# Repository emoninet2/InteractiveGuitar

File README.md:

# InteractiveGuitar

Check documentation on https://github.com/emoninet2/InteractiveGuitar/wiki

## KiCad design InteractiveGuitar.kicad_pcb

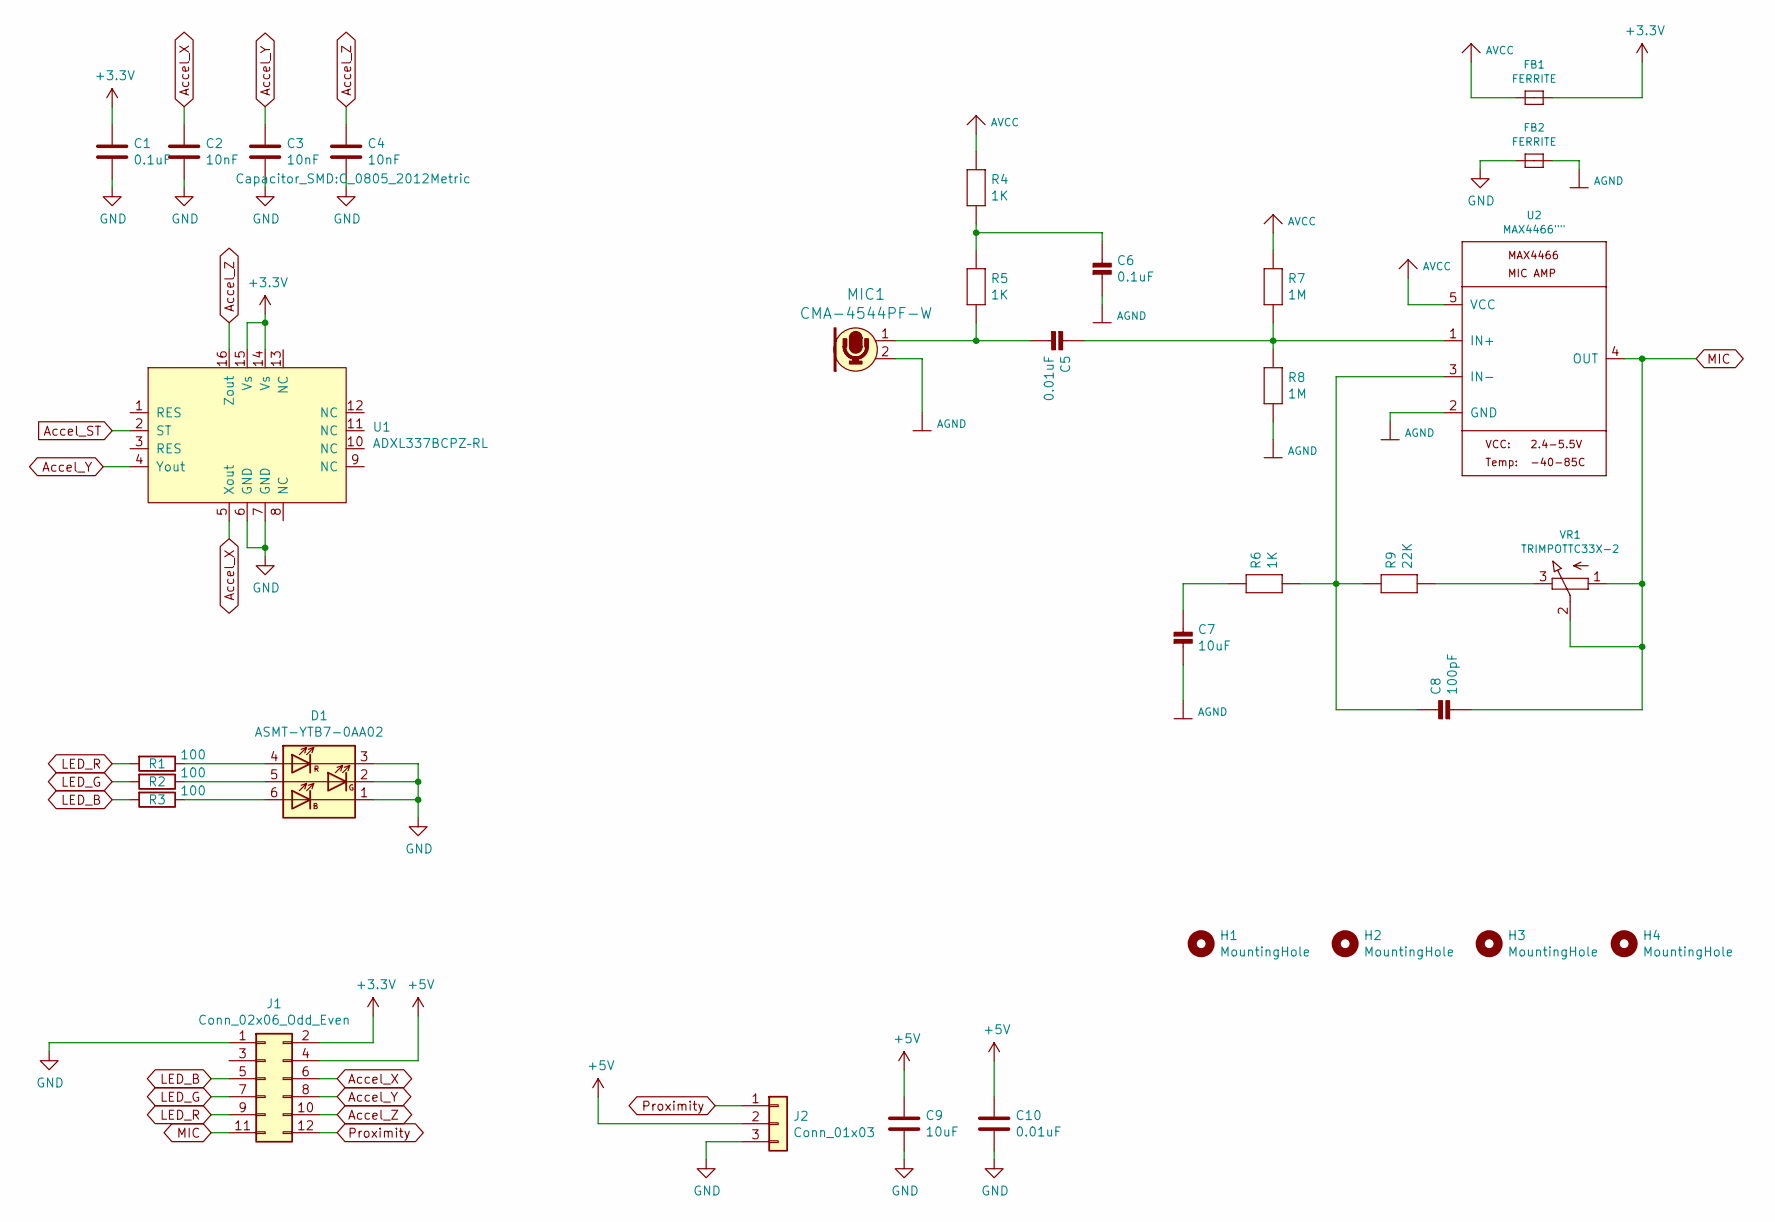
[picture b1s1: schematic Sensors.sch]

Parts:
C1: 0.1uF; C_0805_2012Metric
C2, C3, C4: 10nF; C_0805_2012Metric
C5: 0.01uF; 0805
C6: 0.1uF; 0805
C7: 10uF; 0805
C8: 100pF; 0805
C9: 10uF; C_0805_2012Metric
C10: 0.01uF; C_0805_2012Metric
D1: ASMT-YTB7-0AA02; LED_RGB_5050-6
FB1, FB2: FERRITE; 0805
H1, H2, H3, H4: MountingHole; MountingHole_2.2mm_M2_DIN965_Pad
J1: Conn_02x06_Odd_Even; PinHeader_2x06_P2.54mm_Horizontal
J2: Conn_01x03; PinHeader_1x03_P2.54mm_Horizontal
MIC1: CMA-4544PF-W; ELECTRET_9.7; MPN CMA-4544PF-W; Digi-Key_PN 102-1721-ND
R1, R2, R3: 100; R_0805_2012Metric
R4, R5, R6: 1K; 0805
R7, R8: 1M; 0805
R9: 22K; 0805
U1: ADXL337BCPZ–RL; LFCSP-16-1EP_3x3mm_P0.5mm_EP1.6x1.6mm
U2: MAX4466\"\"; SC70-5
VR1: TRIMPOTTC33X-2; TRIMPOT_BOURNS_TC33X-2

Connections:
+3V3: C1.1, FB1.2, J1.2, U1.14 (Vs), U1.15 (Vs); also elsewhere on the board
+5V: C9.1, C10.1, J1.4, J2.2; also elsewhere on the board
AGND: C6.2, C7.2, FB2.2, MIC1.2, R8.2, U2.2 (GND)
AVCC: FB1.1, R4.1, R7.1, U2.5 (VCC)
Accel_ST: U1.2 (ST)
Accel_X: C2.1, J1.6, U1.5 (Xout)
Accel_Y: C3.1, J1.8, U1.4 (Yout)
Accel_Z: C4.1, J1.10, U1.16 (Zout)
GND: C1.2, C2.2, C3.2, C4.2, C9.2, C10.2, D1.1 (KB), D1.2 (KG), D1.3 (KR), FB2.1, J1.1, J2.3, U1.6 (GND), U1.7 (GND); also elsewhere on the board
LED_B: J1.5, R3.2
LED_G: J1.7, R2.2
LED_R: J1.9, R1.2
MIC: C8.2, J1.11, U2.4 (OUT), VR1.1 (A), VR1.2 (S)
unnamed: C5.1, R7.2, R8.1, U2.1 (IN+)
unnamed: C5.2, MIC1.1, R5.2
unnamed: C6.1, R4.2, R5.1
unnamed: C7.1, R6.1
unnamed: C8.1, R6.2, R9.1, U2.3 (IN-)
unnamed: D1.4 (AR), R1.1
unnamed: D1.5 (AG), R2.1
unnamed: D1.6 (AB), R3.1
unnamed: R9.2, VR1.3 (E)
Proximity: J1.12, J2.1

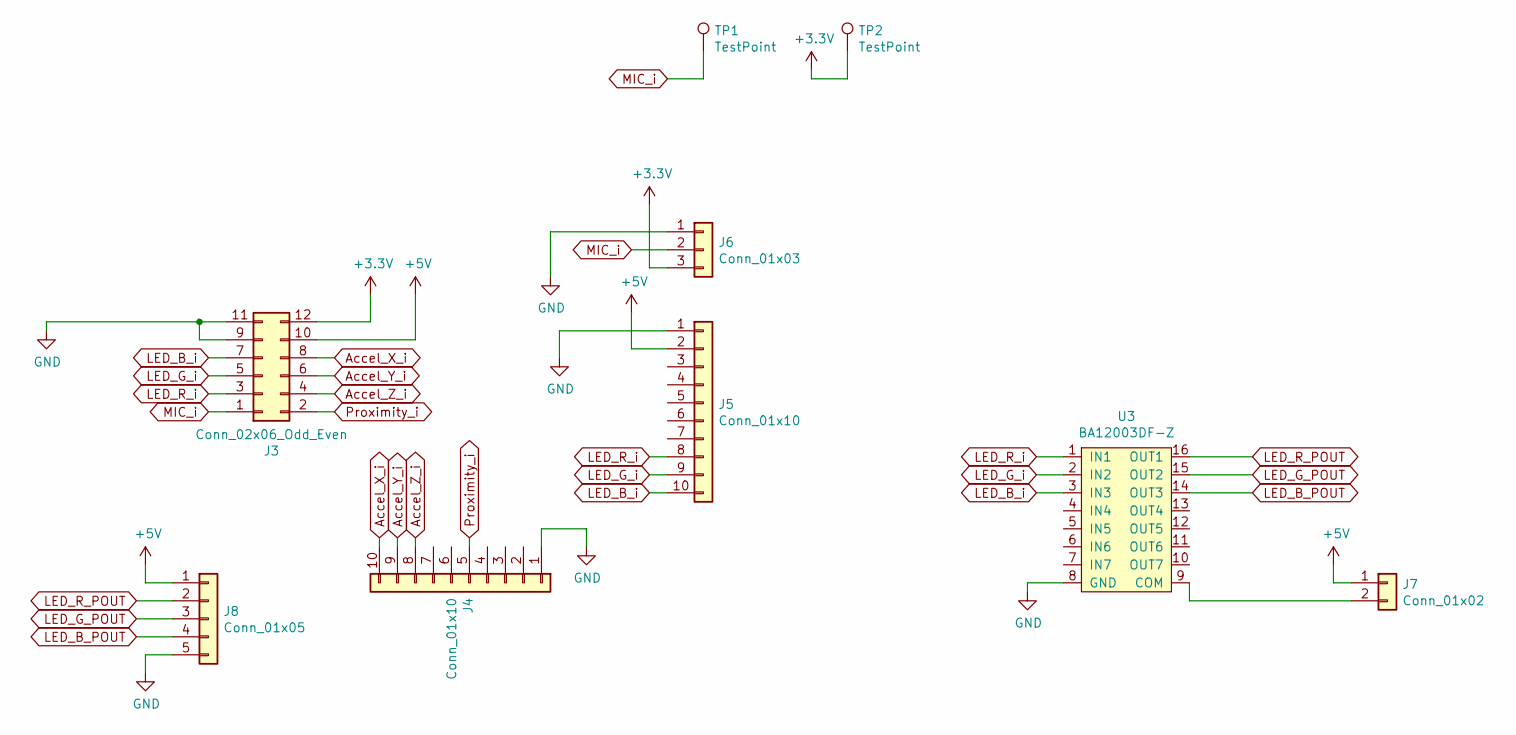
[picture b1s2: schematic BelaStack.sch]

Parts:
J3: Conn_02x06_Odd_Even; PinHeader_2x06_P2.54mm_Horizontal
J4, J5: Conn_01x10; PinHeader_1x10_P2.54mm_Vertical
J6: Conn_01x03; PinHeader_1x03_P2.54mm_Vertical
J7: Conn_01x02; PinHeader_1x02_P2.54mm_Vertical
J8: Conn_01x05; PinHeader_1x05_P2.54mm_Vertical
TP1, TP2: TestPoint; TestPoint_Pad_2.5x2.5mm
U3: BA12003DF-Z; SOIC-16_3.9x9.9mm_P1.27mm

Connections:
+3V3: J3.12, J6.3, TP2.1; also elsewhere on the board
+5V: J3.10, J5.2, J7.1, J8.1; also elsewhere on the board
Accel_X_i: J3.8, J4.10
Accel_Y_i: J3.6, J4.9
Accel_Z_i: J3.4, J4.8
GND: J3.9, J3.11, J4.1, J5.1, J6.1, J8.5, U3.8 (GND); also elsewhere on the board
LED_B_POUT: J8.4, U3.14 (OUT3)
LED_B_i: J3.7, J5.10, U3.3 (IN3)
LED_G_POUT: J8.3, U3.15 (OUT2)
LED_G_i: J3.5, J5.9, U3.2 (IN2)
LED_R_POUT: J8.2, U3.16 (OUT1)
LED_R_i: J3.3, J5.8, U3.1 (IN1)
MIC_i: J3.1, J6.2, TP1.1
unnamed: J7.2, U3.9 (COM)
Proximity_i: J3.2, J4.5

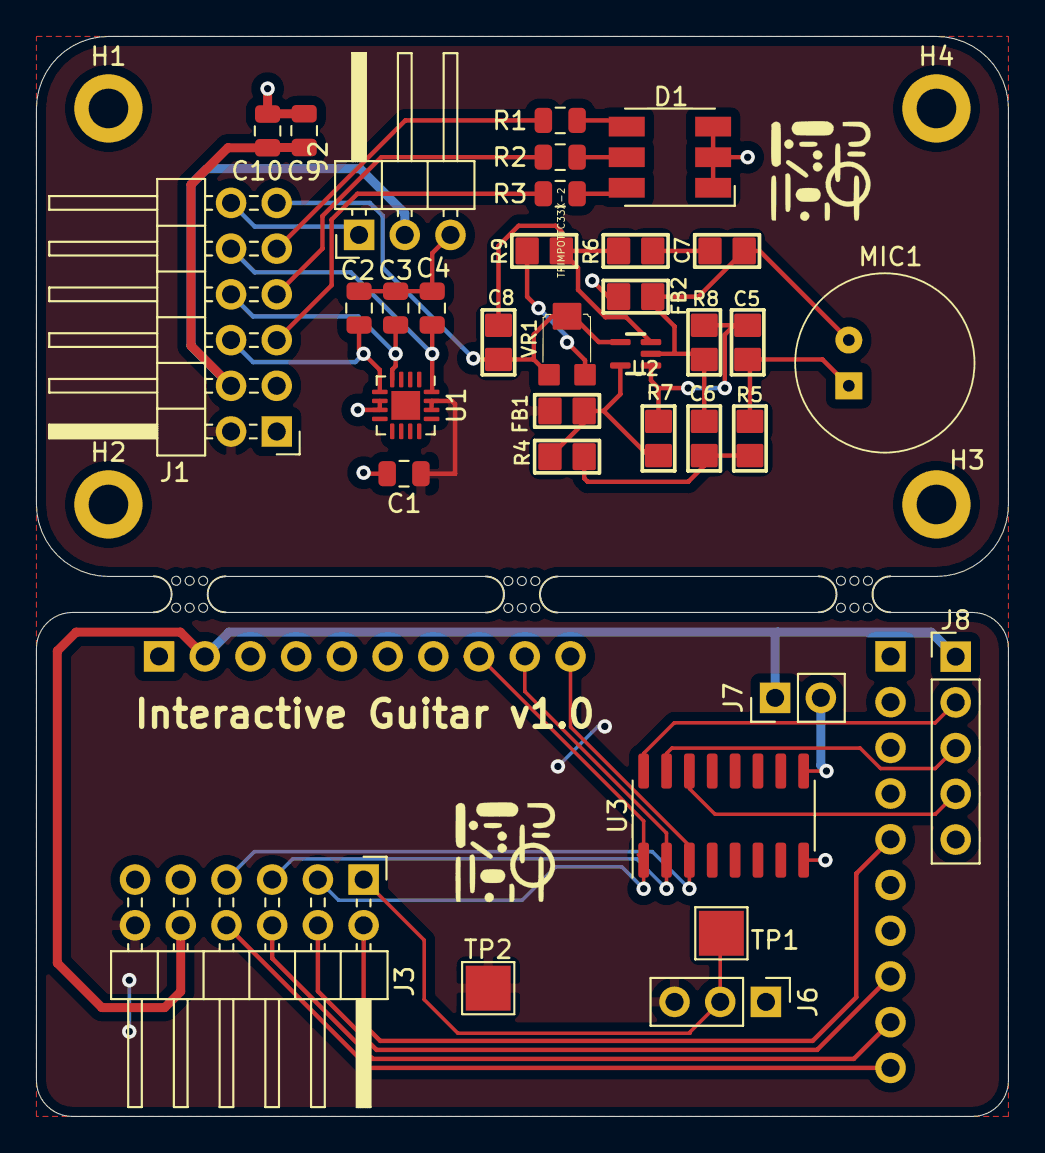
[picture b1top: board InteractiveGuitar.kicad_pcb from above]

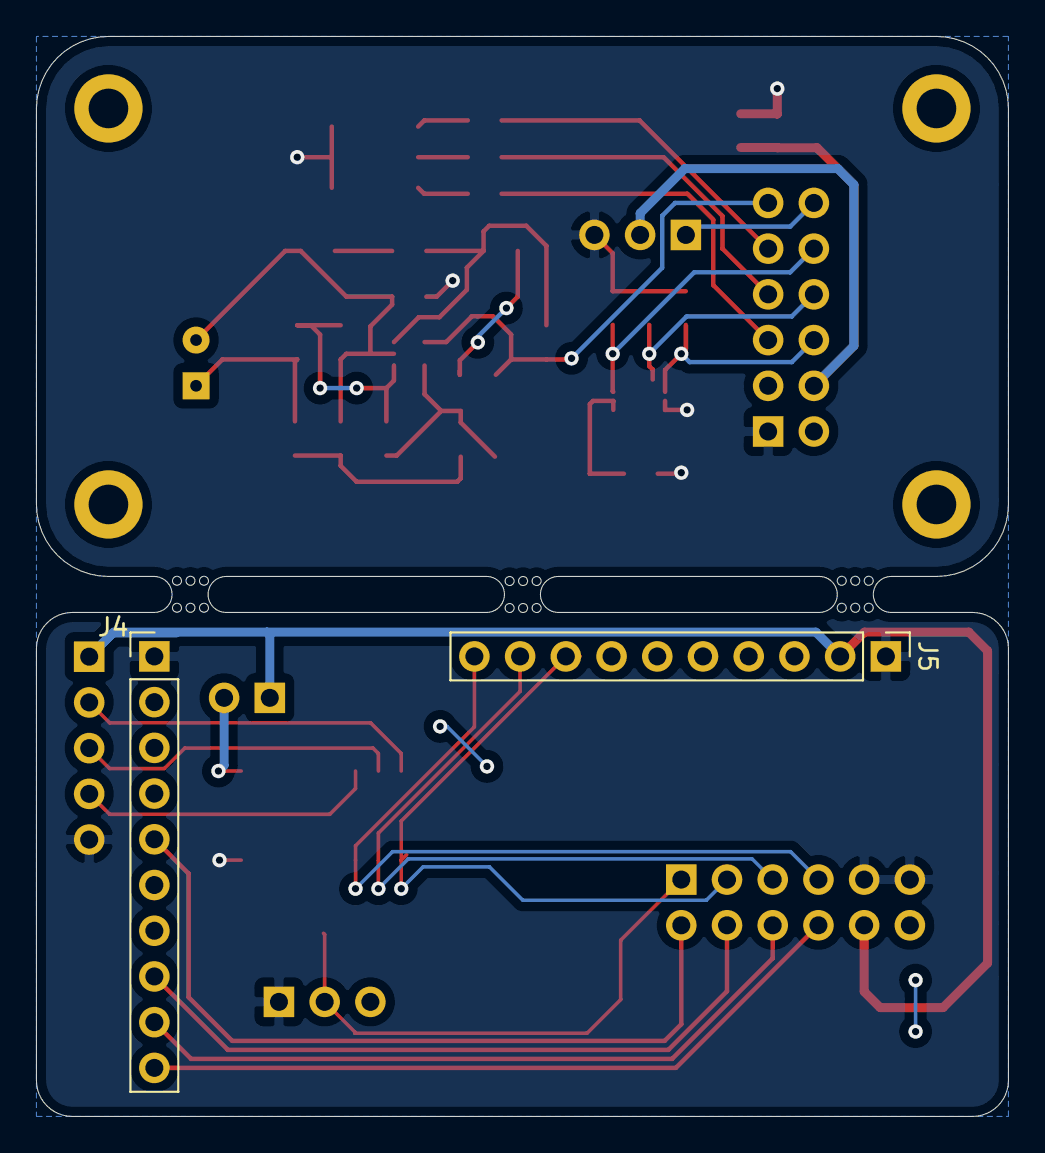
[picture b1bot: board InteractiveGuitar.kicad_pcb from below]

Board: 2 copper layers, 54.0 x 60.0 mm, 44 parts (2 on the bottom side), 34 nets.

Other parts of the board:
mouse-bite-2mm-slot, mouse-bite-2mm-slot#2, mouse-bite-2mm-slot#3: VAL**; mouse-bite-2mm-slot

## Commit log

2020-07-08 added existing project files and folders
2020-07-09 changed connection bits
2020-07-22 fixed mic polarity
2020-09-26 added case design and patch software
2020-09-26 added documentation images
2020-09-27 uploaded documentation image of stencil
2020-09-27 renamed image for bride connection. Added image for PCBOnHeadstock
2020-09-27 added documenttion images for Bela IDE
2020-09-28 added separate stl file for the 3d casing. Added documentation images for cura ide
2020-09-29 added gcode for ultimaker 3
2020-09-29 added documentation images for connections
2020-09-29 added documentation image for pcb pin numbering
